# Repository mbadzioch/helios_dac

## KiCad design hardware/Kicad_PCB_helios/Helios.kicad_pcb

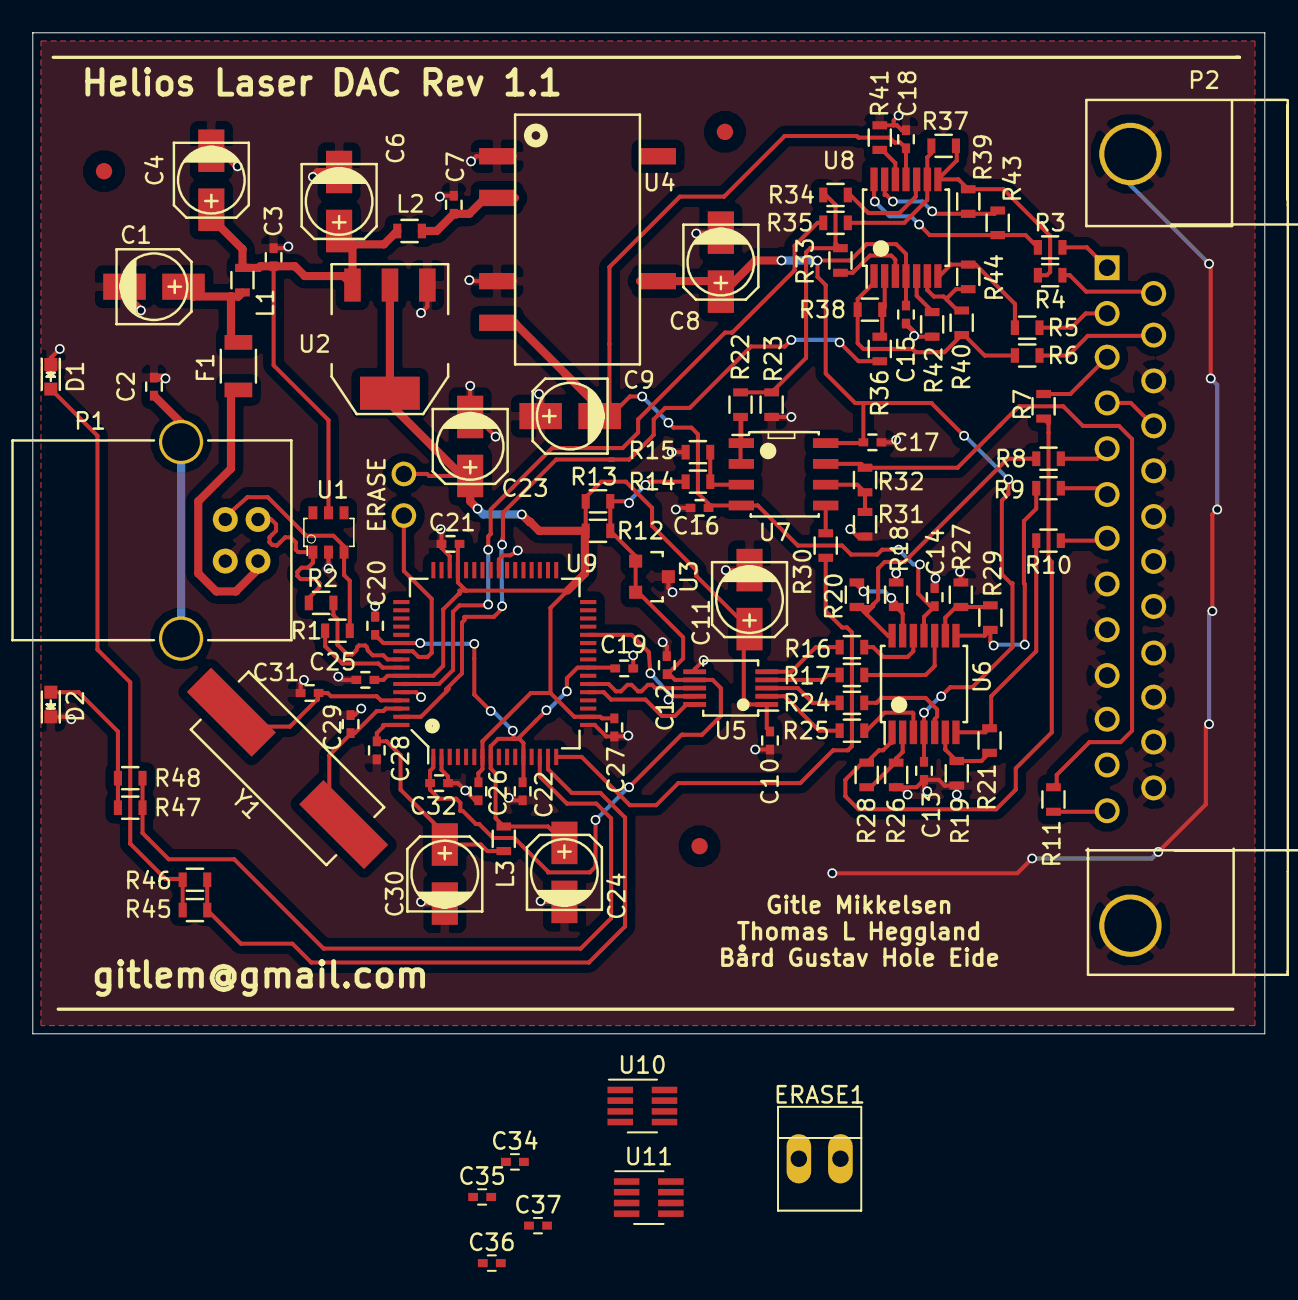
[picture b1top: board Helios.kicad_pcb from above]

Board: 2 copper layers, 75.2 x 61.1 mm, 105 parts (0 on the bottom side), 74 nets.

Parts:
C1, C4, C6, C8, C9, C11, C23, C24, C30: 4.7uF; c_elec_4x5.3
C2, C3, C7, C10, C13, C14, C15, C16, C17, C18, C19, C20, C21, C22, C25, C26, C27, C28, C34, C35: 100nF; C_0402
C12, C29, C31, C32: 13pF; C_0402
C36, C37: 10nF; C_0402
D1, D2: Led_Small; LED_0603
ERASE, ERASE1: CONN_01X02; PINHEAD1-2
F1: F_Small; R_1206
L1, L2, L3: FILTER; R_0603
P1: USB_B
P2: CONN_01X25-SHIELD; DB25
R1, R2: 27; R_0603
R3, R4, R5, R6, R7, R8, R9, R10, R11, R12, R13: 150; R_0603
R14, R15, R18, R19, R20, R21, R23, R26, R27, R28, R29, R31, R37, R38, R39, R40, R43, R44: 10k; R_0603
R16, R17, R24, R25, R30, R32, R41, R42: 5.11k; R_0603
R22, R33, R34, R35, R36, R45, R46, R47, R48: 1.65k; R_0603
U1: IP4220CZ6; SOT457
U2: AP2114; SOT-223
U3: AN431B; SOT-23
U4: ISA_DC-DC_converter; 10-SMD-6
U5: DAC084S085C; MSOP-10_3x3mm_Pitch0.5mm
U6, U8: TL084_v; TSSOP-14_4.4x5mm_Pitch0.65mm
U7: LM358; SOIC-8_3.9x4.9mm_Pitch1.27mm
U9: ATSAM4S; LQFP-64_10x10mm_Pitch0.5mm
U10, U11: DAC8531; SOT-23-8_Handsoldering
Y1: 16MHz 18pF; Crystal_HC49-SD_SMD

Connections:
/2.5V: C12.2, C32.1, R12.2, R13.2, R14.1, U3.1, U3.2, U5.7, U9.1
/3.3V: C10.1, C11.1, C21.1, C23.1, C25.1, C26.1, C27.1, C34.1, C35.1, ERASE1.2, R12.1, R13.1, U2.2, U5.1, U9.7, U9.18, U9.45, U9.58, U10.4, U11.4
/+9V: C8.1, C13.2, C15.2, C17.2, U4.7, U6.4, U7.8, U8.4
/+B: R10.2, R21.1, U6.7
/+G: R9.2, R29.1, U6.8
/+Int: R7.2, R28.1, U6.1
/+R: R8.2, R20.1, U6.14
/+X: R3.2, R43.1, U8.14
/+Y: R5.2, R44.1, U8.7
/-9V: C9.2, C14.2, C16.2, C18.2, U4.5, U6.11, U7.4, U8.11
/-X: R4.2, R37.1, R39.2, U8.8
/-Y: R6.2, R38.1, R40.2, U8.1
/Amplifiers/Offset: R22.2, R23.1, R33.2, R34.2, U8.3, U8.10
/Amplifiers/X: R35.2, U10.1, U10.2
/Amplifiers/Y: R36.2, U11.1, U11.2
/B: R17.2, U5.3
/D+: P1.3, R1.2, U1.3
/D-: P1.2, R2.2, U1.1
/DAC/!SYNC-Quad: U5.9, U9.28
/DAC/!SYNC-X: U9.29, U10.8
/DAC/!SYNC-Y: U9.30, U11.8
/DAC/Din: U5.8, U9.22, U10.6, U11.6
/DAC/SCLK: U5.10, U9.21, U10.7, U11.7
/DAC/X_SCALING: C36.1, U9.59, U10.3
/DAC/Y_SCALING: C37.1, U9.63, U11.3
/G: R24.2, U5.4
/Int: R25.2, U5.2
/Interlock: P2.4, P2.17
/Microcontroller/D+: R1.1, U9.57
/Microcontroller/D-: R2.1, U9.56
/Microcontroller/ERASE: ERASE.1, ERASE1.1, U9.55
/Microcontroller/PA22: R47.1, R48.1, U9.14
/Microcontroller/PA23: R45.1, R46.1, U9.15
/Microcontroller/VDDOUT: C19.1, C20.1, C22.1, C24.1, L3.1, U9.8, U9.12, U9.24, U9.54
/Microcontroller/VDDPLL: C28.1, C30.1, L3.2, U9.64
/Microcontroller/XIN: C29.1, U9.62, Y1.1
/Microcontroller/XOUT: C31.1, U9.61, Y1.2
/R: R16.2, U5.5
/Shutter: R30.2, U9.16
/Shutter_Out: R11.2, R32.1, U7.7
/VCC: C3.1, C4.1, C6.1, L1.2, L2.1, U1.5, U2.3
GND: C1.2, C2.2, C3.2, C4.2, C6.2, C7.2, C8.2, C9.1, C10.2, C11.2, C12.1, C13.1, C14.1, C15.1, C16.1, C17.1, C18.1, C19.2, C20.2, C21.2, C22.2, C23.2, C24.2, C25.2, C26.2, C27.2, C28.2, C29.2, C30.2, C31.2, C32.2, C34.2, C35.2, C36.2, C37.2, D1.1, D2.1, P1.4, P1.5, P2.8, P2.9, P2.10, P2.11, P2.16, P2.18, P2.19, P2.20, P2.21, P2.22, P2.23, P2.24, P2.25, P2.26, R15.2, R18.2, R19.2, R23.2, R26.2, R27.2, R31.1, R41.2, R42.2, U1.2, U2.1, U3.3, U4.1, U4.4, U5.6, U9.2, U9.17, U9.40, U9.46, U9.60, U10.5, U11.5
unnamed: C1.1, F1.2, L1.1
unnamed: C2.1, F1.1, P1.1
unnamed: C7.1, L2.2, U4.2
unnamed: D1.2, R45.2, R46.2
unnamed: D2.2, R47.2, R48.2
unnamed: P2.1, R3.1
unnamed: P2.2, R5.1
unnamed: P2.3, R7.1
unnamed: P2.5, R8.1
unnamed: P2.6, R9.1
unnamed: P2.7, R10.1
unnamed: P2.13, R11.1
unnamed: P2.14, R4.1
unnamed: P2.15, R6.1
unnamed: R14.2, R15.1, U7.3
unnamed: R16.1, U6.12
unnamed: R17.1, U6.5
unnamed: R18.1, R20.2, U6.13
unnamed: R19.1, R21.2, U6.6
unnamed: R22.1, U7.1, U7.2
unnamed: R24.1, U6.10
unnamed: R25.1, U6.3
unnamed: R26.1, R28.2, U6.2
unnamed: R27.1, R29.2, U6.9
unnamed: R30.1, U7.5
unnamed: R31.2, R32.2, U7.6
unnamed: R35.1, R37.2, U8.9
unnamed: R36.1, R38.2, U8.2
unnamed: R39.1, R43.2, U8.13
unnamed: R40.1, R44.2, U8.6
unnamed: R41.1, U8.12
unnamed: R42.1, U8.5

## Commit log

2017-06-05 Dodano 2 zewnętrzne 16 bitowe układy DAC
    Podłączono VREF do wewnętrznych DAC
    Wszystko działa na jednej magistrali SPI
2017-06-14 Updated PCB Layout
    Changed connector to IDC
